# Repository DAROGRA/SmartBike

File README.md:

# SmartBike
 Proyecto Sistemas Embebidos, para mayor informacion visita la Wiki del proyecto

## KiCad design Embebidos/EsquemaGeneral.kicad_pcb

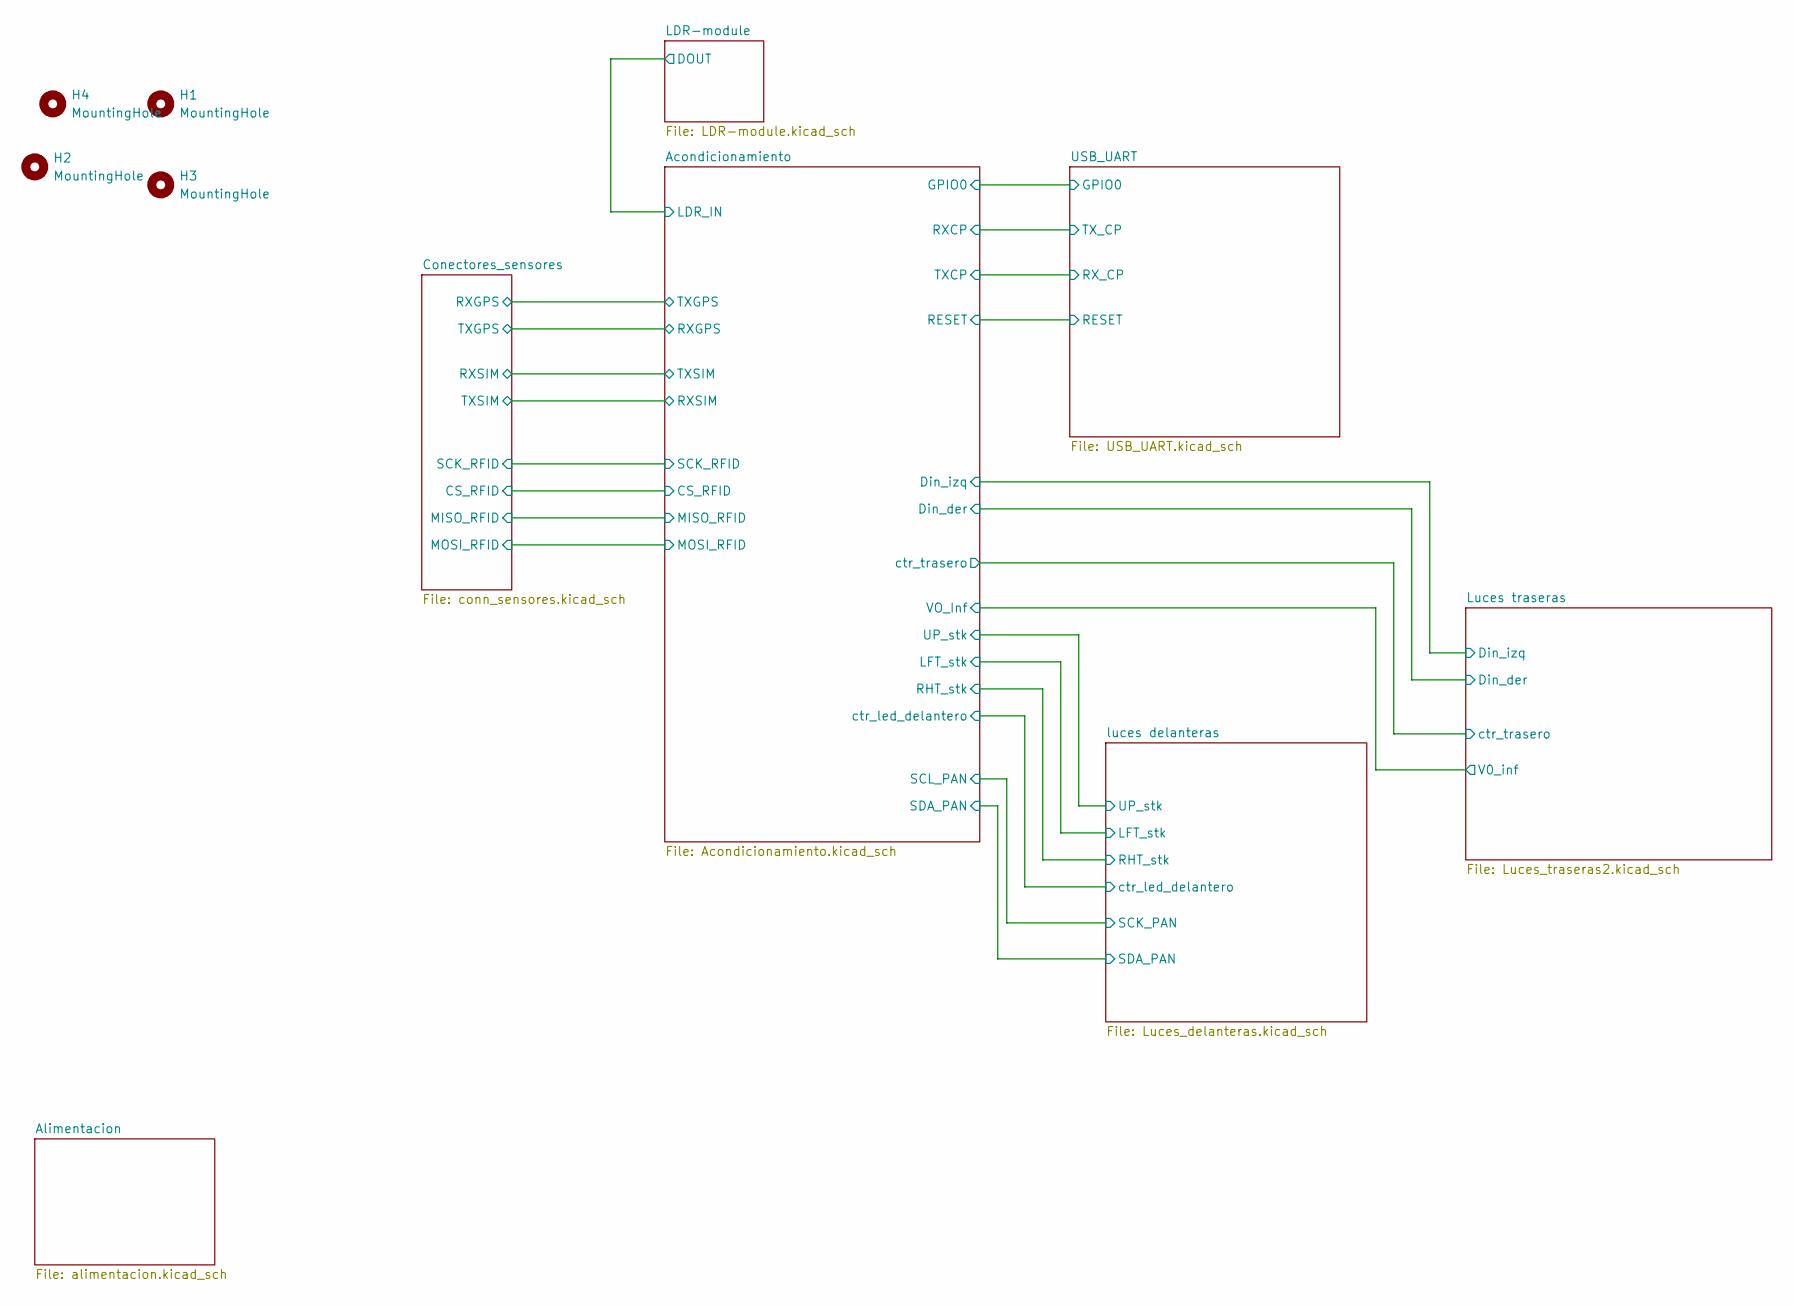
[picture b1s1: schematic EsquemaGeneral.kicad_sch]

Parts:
H1, H2, H3, H4: MountingHole; MountingHole_2.2mm_M2

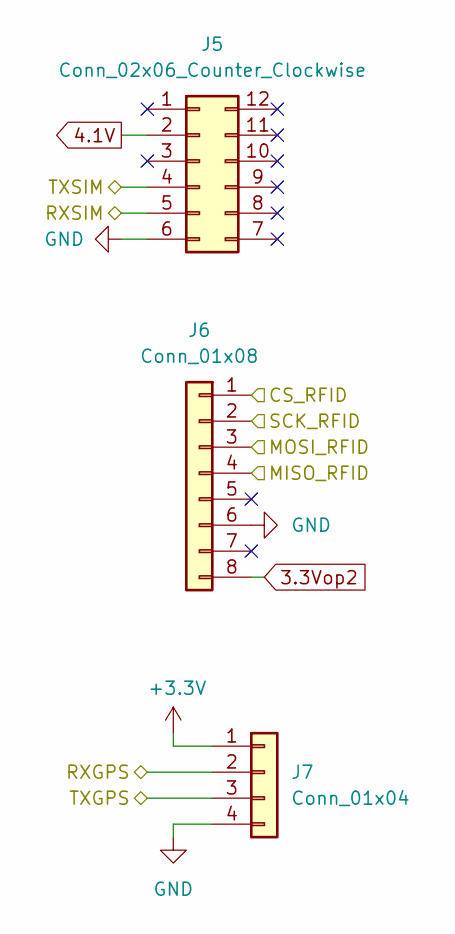
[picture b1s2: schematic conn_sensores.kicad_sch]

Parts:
J5: Conn_02x06_Counter_Clockwise; sim800l
J6: Conn_01x08; JST_EH_S8B-EH_1x08_P2.50mm_Horizontal
J7: Conn_01x04; JST_EH_B4B-EH-A_1x04_P2.50mm_Vertical

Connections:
3.3Vop2: J6.8; also elsewhere on the board
4.1V: J5.2; also elsewhere on the board
+3.3V: J7.1; also elsewhere on the board
/Acondicionamiento/CS_RFID: J6.1; also elsewhere on the board
/Acondicionamiento/MISO_RFID: J6.4; also elsewhere on the board
/Acondicionamiento/MOSI_RFID: J6.3; also elsewhere on the board
/Acondicionamiento/RXGPS: J7.3; also elsewhere on the board
/Acondicionamiento/RXSIM: J5.4; also elsewhere on the board
/Acondicionamiento/SCK_RFID: J6.2; also elsewhere on the board
/Acondicionamiento/TXGPS: J7.2; also elsewhere on the board
/Acondicionamiento/TXSIM: J5.5; also elsewhere on the board
GND: J5.6, J6.6, J7.4; also elsewhere on the board

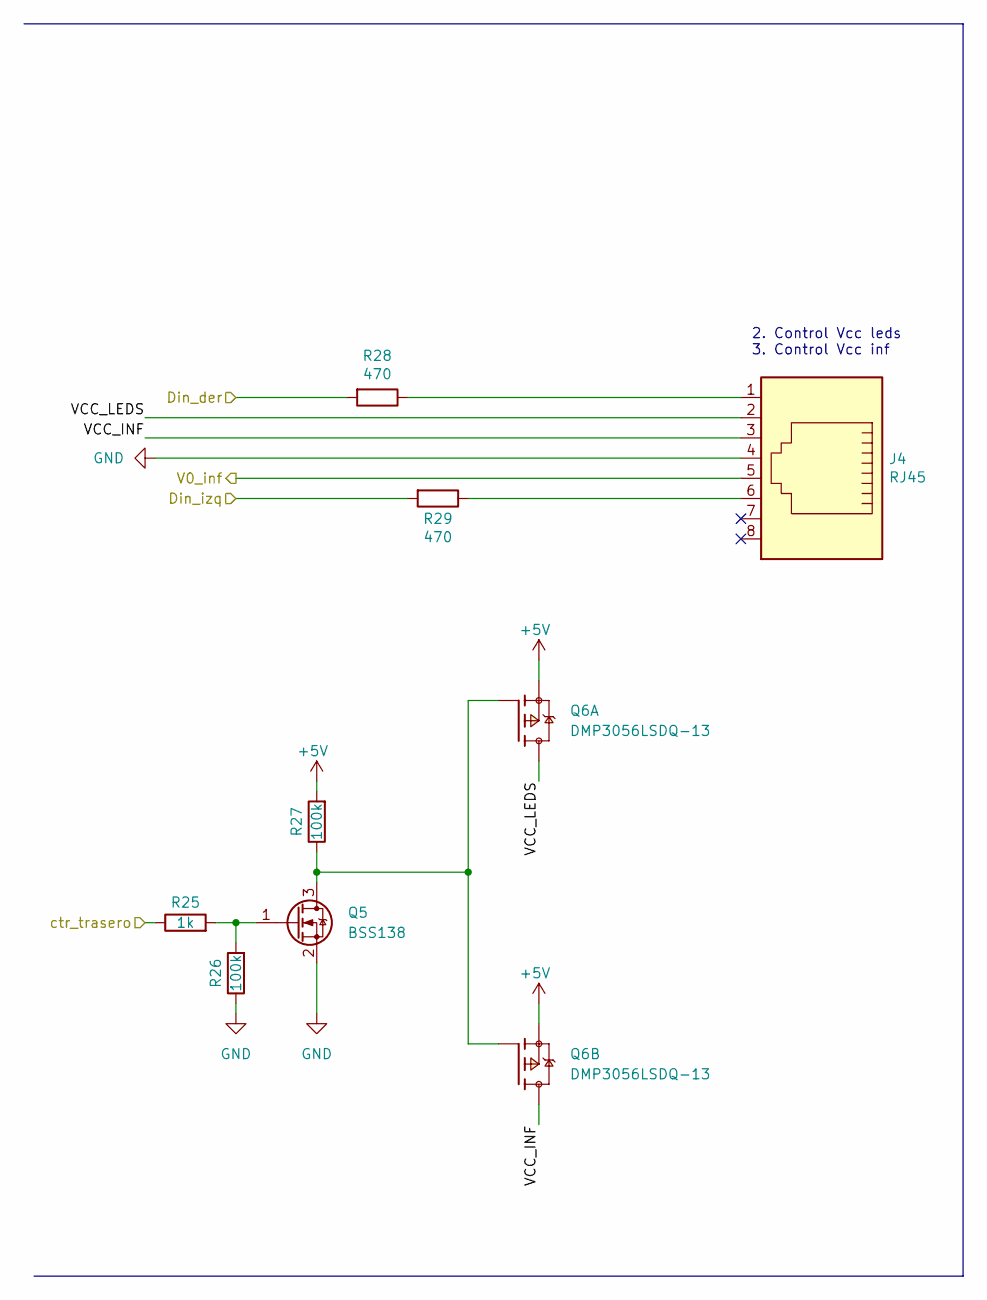
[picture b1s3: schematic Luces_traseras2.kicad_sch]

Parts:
J4: RJ45; RJ45_Amphenol_54602-x08_Horizontal
Q5: BSS138; SOT-23
Q6: DMP3056LSDQ-13; SOIC127P600X175-8N; PARTREV 1-2
R25: 1k; R_0805_2012Metric_Pad1.20x1.40mm_HandSolder
R26, R27: 100k; R_0805_2012Metric_Pad1.20x1.40mm_HandSolder
R28, R29: 470; R_0805_2012Metric_Pad1.20x1.40mm_HandSolder

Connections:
+5V: Q6.1, Q6.3, R27.2; also elsewhere on the board
/Acondicionamiento/Din_der: R28.2; also elsewhere on the board
/Acondicionamiento/Din_izq: R29.2; also elsewhere on the board
/Acondicionamiento/VO_Inf: J4.5; also elsewhere on the board
/Acondicionamiento/ctr_trasero: R25.1; also elsewhere on the board
/Luces traseras/VCC_INF: J4.3, Q6.5, Q6.6
/Luces traseras/VCC_LEDS: J4.2, Q6.7, Q6.8
GND: J4.4, Q5.2 (S), R26.1; also elsewhere on the board
unnamed: J4.1, R28.1
unnamed: J4.6, R29.1
unnamed: Q5.1 (G), R25.2, R26.2
unnamed: Q5.3 (D), Q6.2, Q6.4, R27.1

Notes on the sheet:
2. Control Vcc leds 3. Control Vcc inf

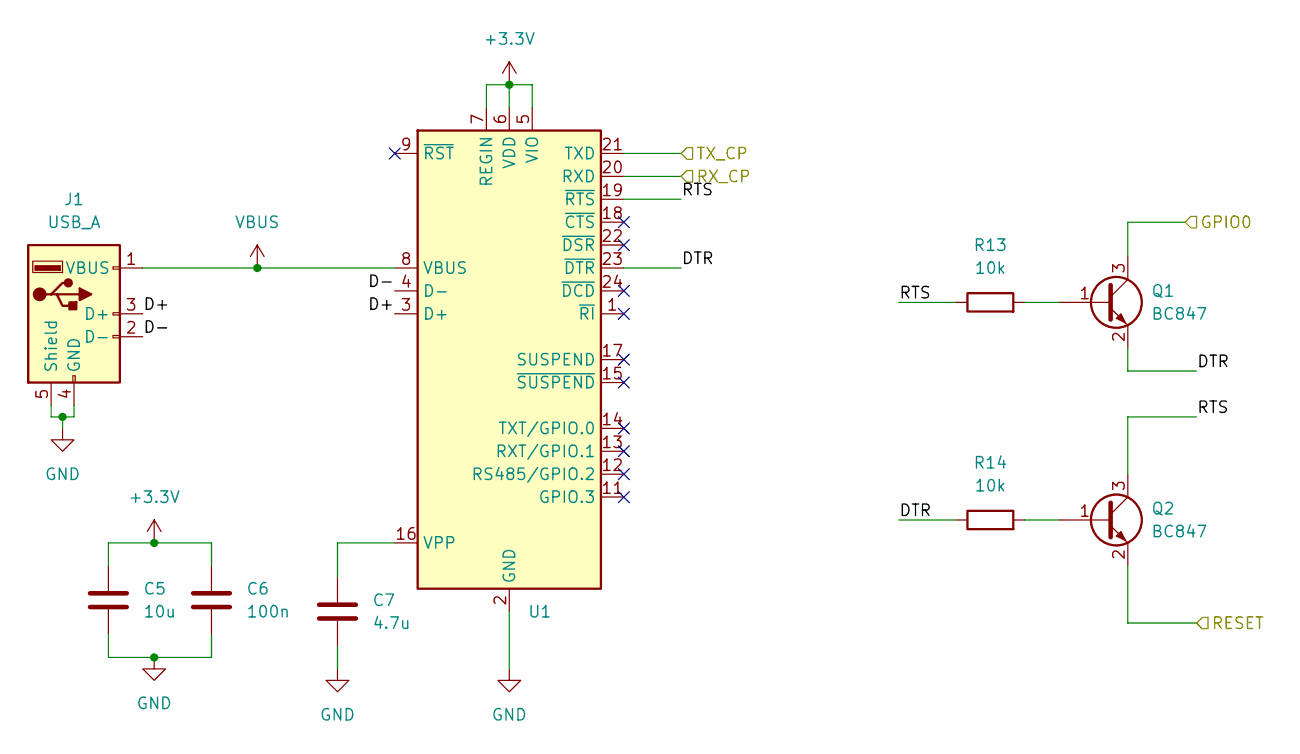
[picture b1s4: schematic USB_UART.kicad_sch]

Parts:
C5: 10u; C_0805_2012Metric_Pad1.18x1.45mm_HandSolder
C6: 100n; C_0805_2012Metric_Pad1.18x1.45mm_HandSolder
C7: 4.7u; C_0805_2012Metric_Pad1.18x1.45mm_HandSolder
J1: USB_A; USB_A_CNCTech_1001-011-01101_Horizontal
Q1, Q2: BC847; SOT23
R13, R14: 10k; R_0805_2012Metric_Pad1.20x1.40mm_HandSolder
U1: QFN50P400X400X80-25N

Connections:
+3.3V: C5.1, C6.1, U1.5 (VIO), U1.6 (VDD), U1.7 (REGIN); also elsewhere on the board
/Acondicionamiento/GPIO0: Q1.3 (C); also elsewhere on the board
/Acondicionamiento/RESET: Q2.2 (E); also elsewhere on the board
/Acondicionamiento/RXCP: U1.21 (TXD); also elsewhere on the board
/Acondicionamiento/TXCP: U1.20 (RXD); also elsewhere on the board
/USB_UART/D+: J1.3 (D+), U1.3 (D+)
/USB_UART/D-: J1.2 (D-), U1.4 (D-)
/USB_UART/DTR: Q1.2 (E), R14.1, U1.23 (~DTR)
/USB_UART/RTS: Q2.3 (C), R13.1, U1.19 (~RTS)
GND: C5.2, C6.2, C7.2, J1.4 (GND), J1.5 (Shield), U1.2 (GND), U1.25 (GND); also elsewhere on the board
unnamed: C7.1, U1.16 (VPP)
unnamed: Q1.1 (B), R13.2
unnamed: Q2.1 (B), R14.2
VBUS: J1.1 (VBUS), U1.8 (VBUS)

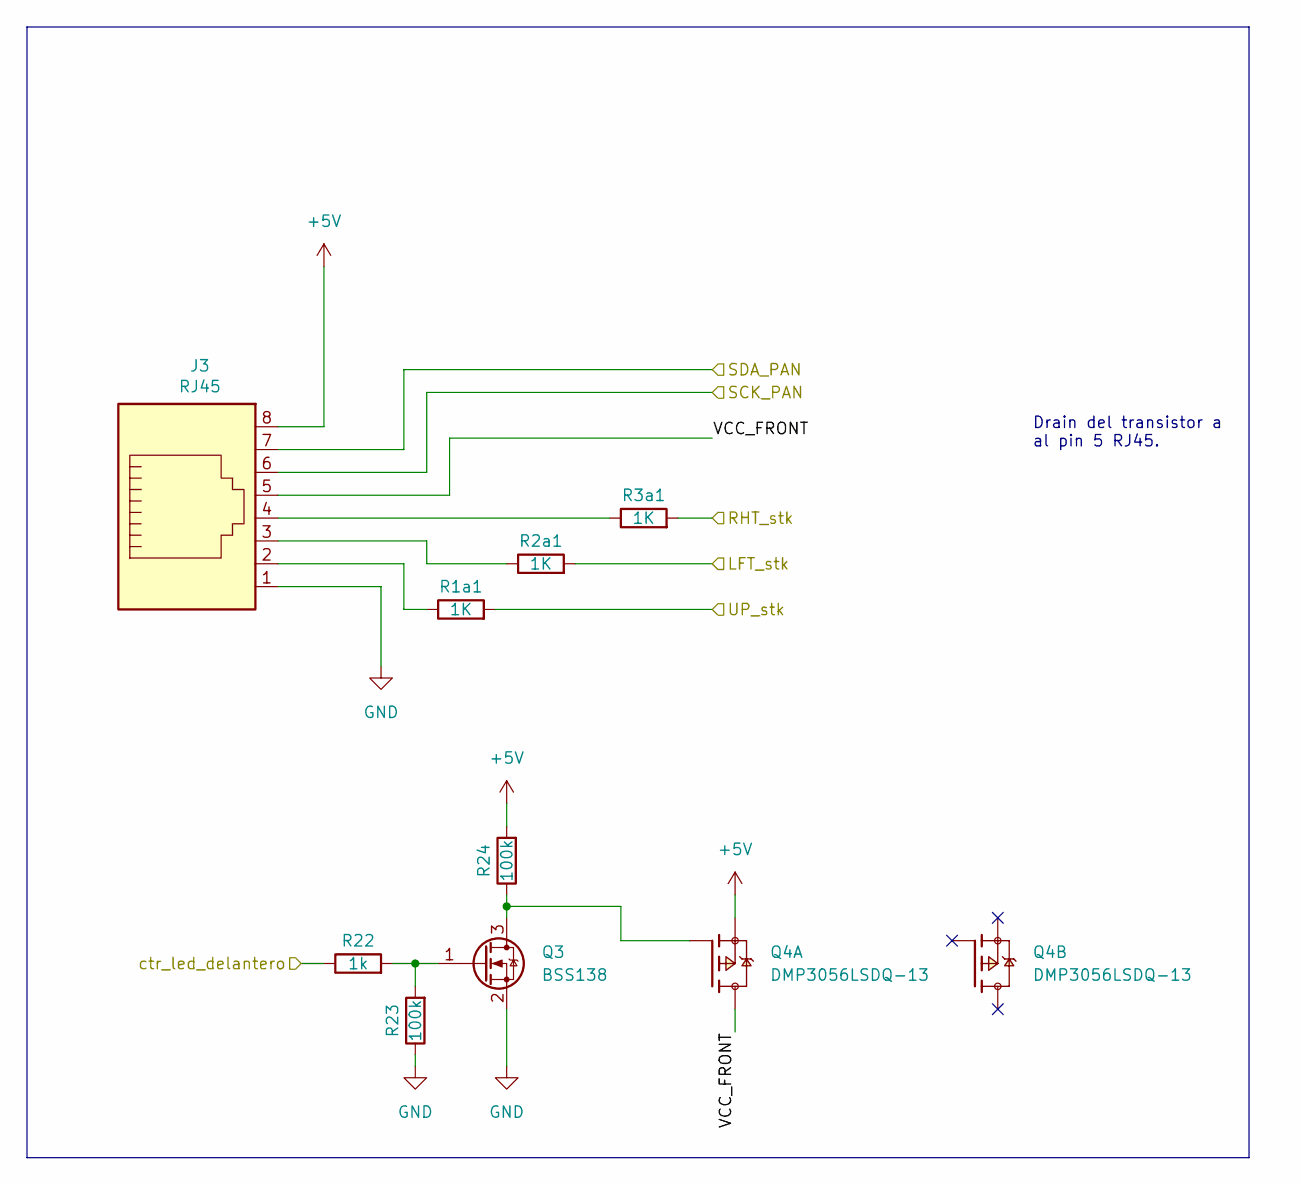
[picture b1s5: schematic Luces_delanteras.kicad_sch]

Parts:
J3: RJ45; RJ45_Amphenol_54602-x08_Horizontal
Q3: BSS138; SOT-23
Q4: DMP3056LSDQ-13; SOIC127P600X175-8N; PARTREV 1-2
R1a1, R2a1, R3a1: 1K; R_0805_2012Metric_Pad1.20x1.40mm_HandSolder
R22: 1k; R_0805_2012Metric_Pad1.20x1.40mm_HandSolder
R23, R24: 100k; R_0805_2012Metric_Pad1.20x1.40mm_HandSolder

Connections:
+5V: J3.8, Q4.1, R24.2; also elsewhere on the board
/Acondicionamiento/LFT_stk: R2a1.2; also elsewhere on the board
/Acondicionamiento/RHT_stk: R3a1.2; also elsewhere on the board
/Acondicionamiento/SCL_PAN: J3.6; also elsewhere on the board
/Acondicionamiento/SDA_PAN: J3.7; also elsewhere on the board
/Acondicionamiento/UP_stk: R1a1.2; also elsewhere on the board
/Acondicionamiento/ctr_led_delantero: R22.1; also elsewhere on the board
/luces delanteras/VCC_FRONT: J3.5, Q4.7, Q4.8
GND: J3.1, Q3.2 (S), R23.1; also elsewhere on the board
unnamed: J3.2, R1a1.1
unnamed: J3.3, R2a1.1
unnamed: J3.4, R3a1.1
unnamed: Q3.1 (G), R22.2, R23.2
unnamed: Q3.3 (D), Q4.2, R24.1

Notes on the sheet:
Drain del transistor a al pin 5 RJ45.

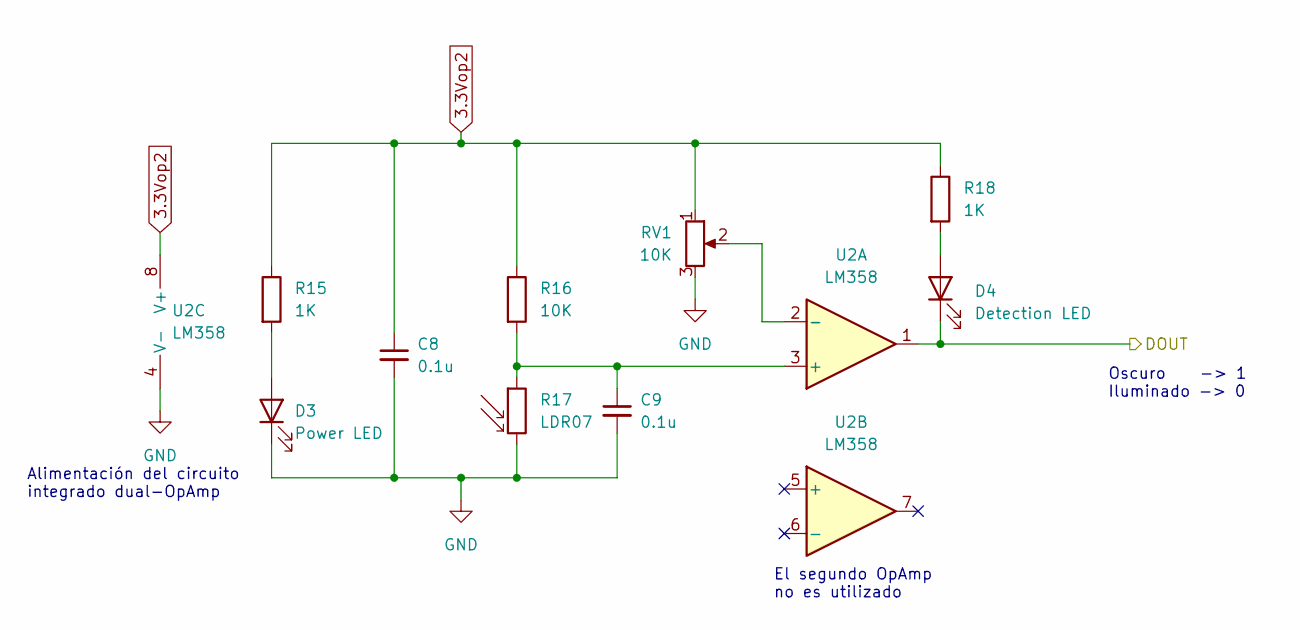
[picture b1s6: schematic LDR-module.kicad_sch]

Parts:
C8, C9: 0.1u; C_0805_2012Metric_Pad1.18x1.45mm_HandSolder
D3: Power LED; LED_0805_2012Metric_Pad1.15x1.40mm_HandSolder
D4: Detection LED; LED_0805_2012Metric_Pad1.15x1.40mm_HandSolder
R15, R18: 1K; R_0805_2012Metric_Pad1.20x1.40mm_HandSolder
R16: 10K; R_0805_2012Metric_Pad1.20x1.40mm_HandSolder
R17: LDR07; R_LDR_5.1x4.3mm_P3.4mm_Vertical
RV1: 10K; Potentiometer_Bourns_3386P_Vertical
U2: LM358; SOIC127P599X175-8N

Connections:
3.3Vop2: C8.1, R15.1, R16.1, R18.1, RV1.1, U2.8 (V+); also elsewhere on the board
/Acondicionamiento/LDR_IN: D4.1 (K), U2.1; also elsewhere on the board
GND: C8.2, C9.2, D3.1 (K), R17.2, RV1.3, U2.4 (V-); also elsewhere on the board
unnamed: C9.1, R16.2, R17.1, U2.3 (+)
unnamed: D3.2 (A), R15.2
unnamed: D4.2 (A), R18.2
unnamed: RV1.2, U2.2 (-)

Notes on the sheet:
El segundo OpAmp no es utilizado
Alimentación del circuito integrado dual-OpAmp
Oscuro -> 1 Iluminado -> 0

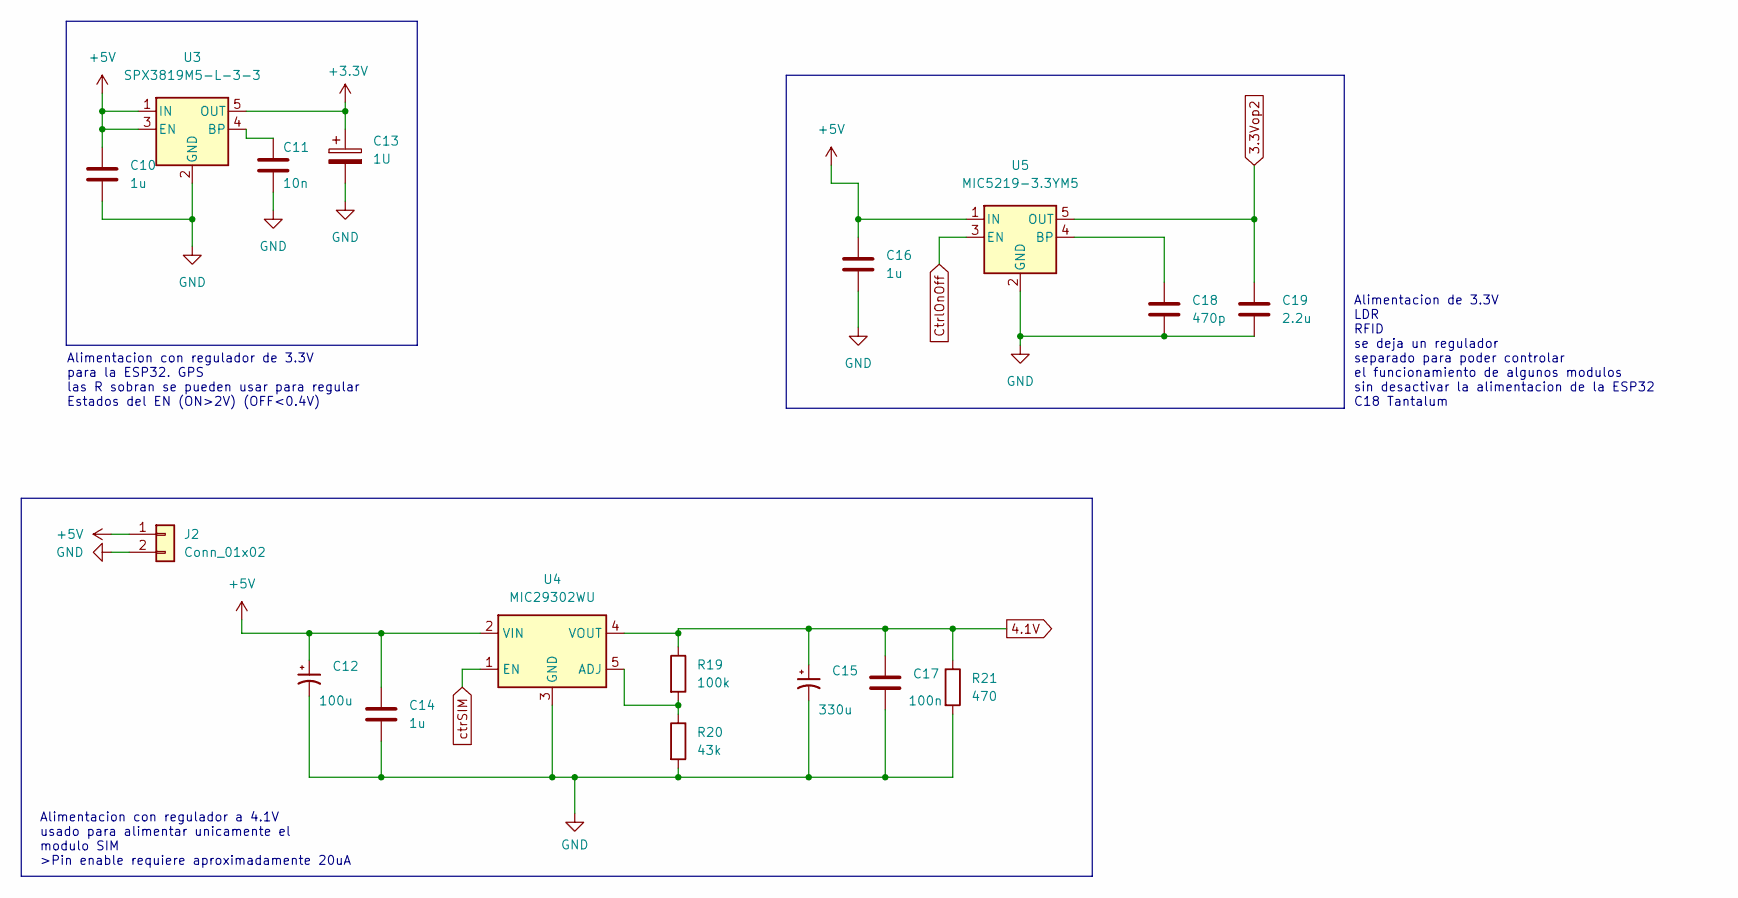
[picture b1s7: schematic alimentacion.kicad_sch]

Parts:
C10, C14, C16: 1u; C_0805_2012Metric_Pad1.18x1.45mm_HandSolder
C11: 10n; C_0805_2012Metric_Pad1.18x1.45mm_HandSolder
C12: 100u; CP_EIA-6032-28_Kemet-C_Pad2.25x2.35mm_HandSolder
C13: 1U; CP_EIA-3216-18_Kemet-A_Pad1.58x1.35mm_HandSolder
C15: 330u; CP_Elec_8x10.5
C17: 100n; C_0805_2012Metric_Pad1.18x1.45mm_HandSolder
C18: 470p; C_0805_2012Metric_Pad1.18x1.45mm_HandSolder
C19: 2.2u; CP_EIA-3216-18_Kemet-A_Pad1.58x1.35mm_HandSolder
J2: Conn_01x02; JST_EH_S2B-EH_1x02_P2.50mm_Horizontal
R19: 100k; R_0805_2012Metric_Pad1.20x1.40mm_HandSolder
R20: 43k; R_1206_3216Metric_Pad1.30x1.75mm_HandSolder
R21: 470; R_0805_2012Metric_Pad1.20x1.40mm_HandSolder
U3: SPX3819M5-L-3-3; SOT-23-5
U4: MIC29302WU; TO-263-5_TabPin3
U5: MIC5219-3.3YM5; SOT-23-5

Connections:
3.3Vop2: C19.1, U5.5 (OUT); also elsewhere on the board
4.1V: C15.1, C17.1, R19.1, R21.1, U4.4 (VOUT); also elsewhere on the board
+3.3V: C13.1, U3.5 (OUT); also elsewhere on the board
+5V: C10.1, C12.1, C14.1, C16.1, J2.1, U3.1 (IN), U3.3 (EN), U4.2 (VIN), U5.1 (IN); also elsewhere on the board
CtrlOnOff: U5.3 (EN); also elsewhere on the board
GND: C10.2, C11.2, C12.2, C13.2, C14.2, C15.2, C16.2, C17.2, C18.2, C19.2, J2.2, R20.2, R21.2, U3.2 (GND), U4.3 (GND), U5.2 (GND); also elsewhere on the board
unnamed: C11.1, U3.4 (BP)
unnamed: C18.1, U5.4 (BP)
unnamed: R19.2, R20.1, U4.5 (ADJ)
ctrSIM: U4.1 (EN); also elsewhere on the board

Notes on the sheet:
Alimentacion de 3.3V LDR RFID se deja un regulador separado para poder controlar el funcionamiento de algunos modulos sin desactivar la alimentacion de la ESP32 C18 Tantalum
Alimentacion con regulador a 4.1V usado para alimentar unicamente el modulo SIM >Pin enable requiere aproximadamente 20uA
Alimentacion con regulador de 3.3V para la ESP32. GPS las R sobran se pueden usar para regular Estados del EN (ON>2V) (OFF<0.4V)

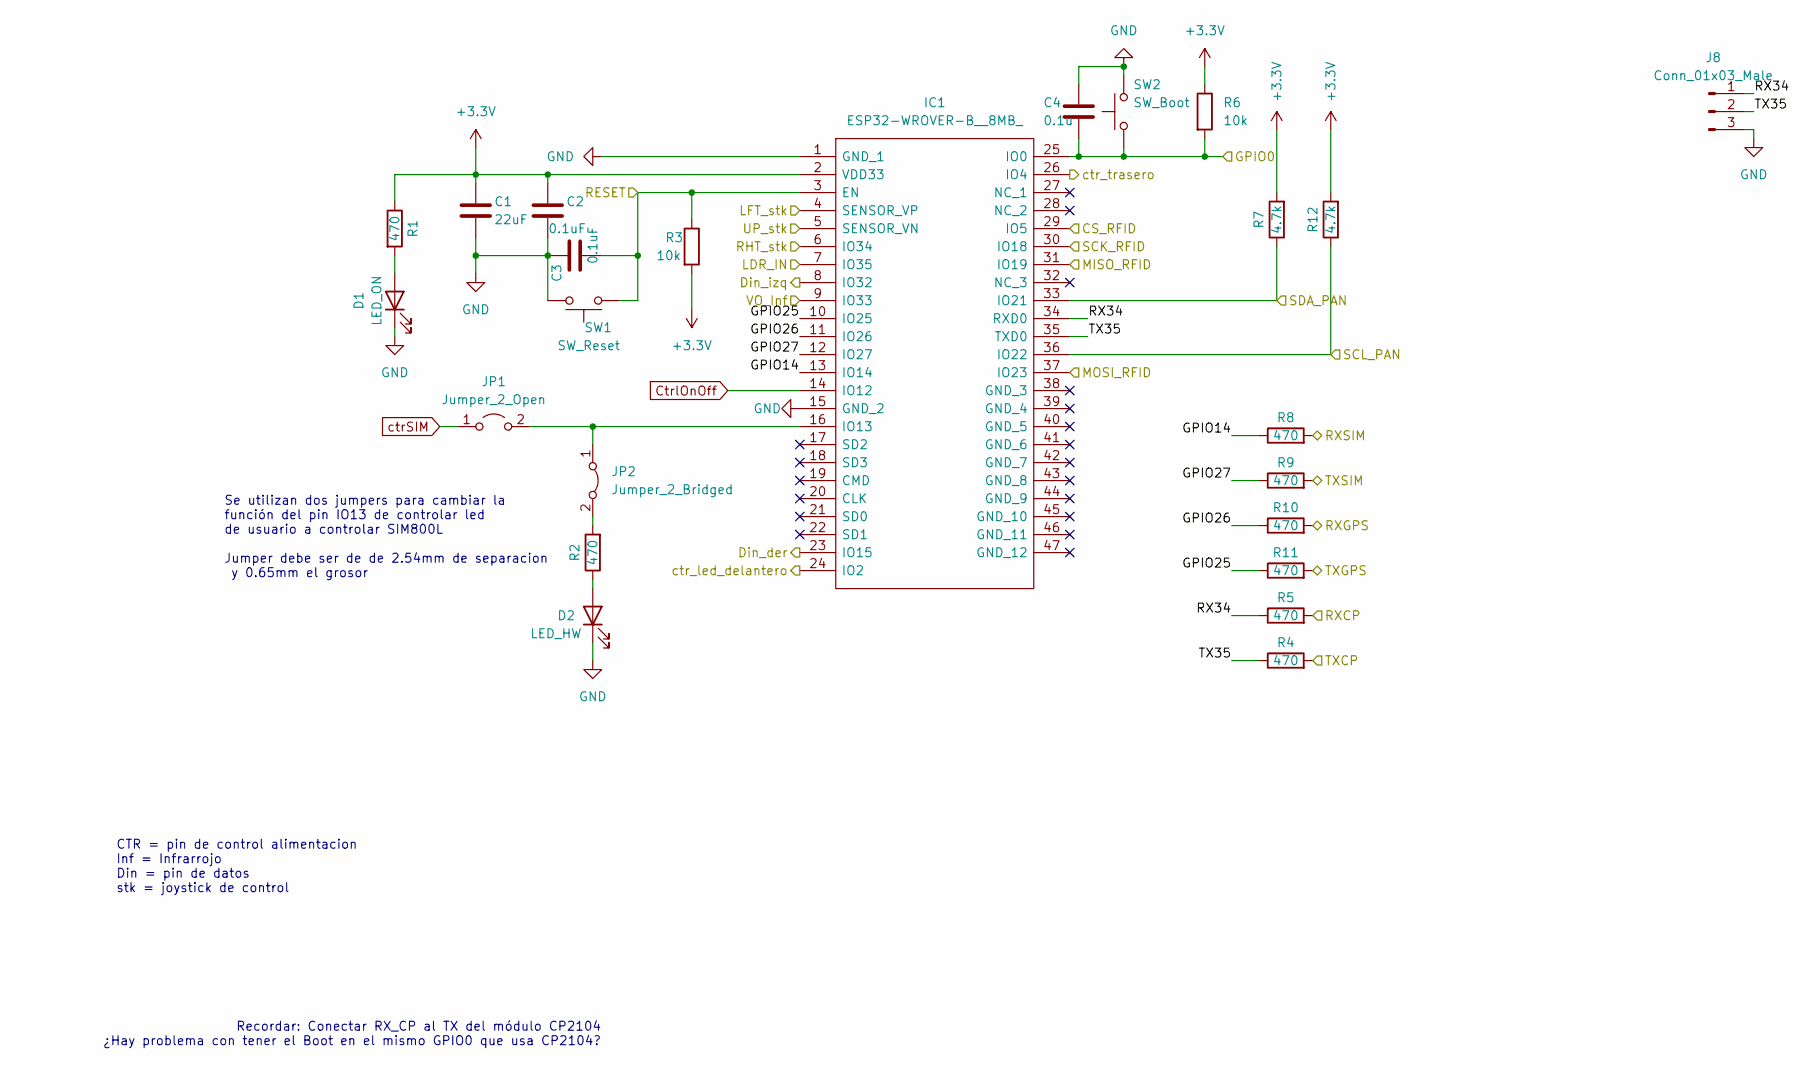
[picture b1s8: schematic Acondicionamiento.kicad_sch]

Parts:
C1: 22uF; C_0805_2012Metric_Pad1.18x1.45mm_HandSolder
C2, C3: 0.1uF; C_0805_2012Metric_Pad1.18x1.45mm_HandSolder
C4: 0.1u; C_0805_2012Metric_Pad1.18x1.45mm_HandSolder
D1: LED_ON; LED_0805_2012Metric_Pad1.15x1.40mm_HandSolder
D2: LED_HW; LED_0805_2012Metric_Pad1.15x1.40mm_HandSolder
IC1: ESP32-WROVER-B__8MB_; ESP32WROVERB8MB; Manufacturer_Part_Number ESP32-WROVER-B (8MB); Mouser Part Number 356-ESP32-WRO-B(8MB)
J8: Conn_01x03_Male; PinHeader_1x03_P2.54mm_Vertical
JP1: Jumper_2_Open; PinHeader_1x02_P2.54mm_Vertical
JP2: Jumper_2_Bridged; PinHeader_1x02_P2.54mm_Vertical
R1, R2, R4, R5, R8, R9, R10, R11: 470; R_0805_2012Metric_Pad1.20x1.40mm_HandSolder
R3, R6: 10k; R_0805_2012Metric_Pad1.20x1.40mm_HandSolder
R7, R12: 4.7k; R_0805_2012Metric_Pad1.20x1.40mm_HandSolder
SW1: SW_Reset; pulsador
SW2: SW_Boot; pulsador

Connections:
+3.3V: C1.1, C2.1, IC1.2 (VDD33), R1.1, R3.2, R6.1, R7.2, R12.2; also elsewhere on the board
/Acondicionamiento/CS_RFID: IC1.29 (IO5); also elsewhere on the board
/Acondicionamiento/Din_der: IC1.23 (IO15); also elsewhere on the board
/Acondicionamiento/Din_izq: IC1.8 (IO32); also elsewhere on the board
/Acondicionamiento/GPIO0: C4.2, IC1.25 (IO0), R6.2, SW2.1; also elsewhere on the board
/Acondicionamiento/GPIO14: IC1.13 (IO14), R8.1
/Acondicionamiento/GPIO25: IC1.10 (IO25), R11.1
/Acondicionamiento/GPIO26: IC1.11 (IO26), R10.1
/Acondicionamiento/GPIO27: IC1.12 (IO27), R9.1
/Acondicionamiento/LDR_IN: IC1.7 (IO35); also elsewhere on the board
/Acondicionamiento/LFT_stk: IC1.4 (SENSOR_VP); also elsewhere on the board
/Acondicionamiento/MISO_RFID: IC1.31 (IO19); also elsewhere on the board
/Acondicionamiento/MOSI_RFID: IC1.37 (IO23); also elsewhere on the board
/Acondicionamiento/RESET: C3.2, IC1.3 (EN), R3.1, SW1.1; also elsewhere on the board
/Acondicionamiento/RHT_stk: IC1.6 (IO34); also elsewhere on the board
/Acondicionamiento/RX34: IC1.34 (RXD0), J8.1, R5.1
/Acondicionamiento/RXCP: R5.2; also elsewhere on the board
/Acondicionamiento/RXGPS: R10.2; also elsewhere on the board
/Acondicionamiento/RXSIM: R8.2; also elsewhere on the board
/Acondicionamiento/SCK_RFID: IC1.30 (IO18); also elsewhere on the board
/Acondicionamiento/SCL_PAN: IC1.36 (IO22), R12.1; also elsewhere on the board
/Acondicionamiento/SDA_PAN: IC1.33 (IO21), R7.1; also elsewhere on the board
/Acondicionamiento/TX35: IC1.35 (TXD0), J8.2, R4.1
/Acondicionamiento/TXCP: R4.2; also elsewhere on the board
/Acondicionamiento/TXGPS: R11.2; also elsewhere on the board
/Acondicionamiento/TXSIM: R9.2; also elsewhere on the board
/Acondicionamiento/UP_stk: IC1.5 (SENSOR_VN); also elsewhere on the board
/Acondicionamiento/VO_Inf: IC1.9 (IO33); also elsewhere on the board
/Acondicionamiento/ctr_led_delantero: IC1.24 (IO2); also elsewhere on the board
/Acondicionamiento/ctr_trasero: IC1.26 (IO4); also elsewhere on the board
CtrlOnOff: IC1.14 (IO12); also elsewhere on the board
GND: C1.2, C2.2, C3.1, C4.1, D1.1 (K), D2.1 (K), IC1.1 (GND_1), IC1.15 (GND_2), J8.3, SW1.2, SW2.2; also elsewhere on the board
unnamed: D1.2 (A), R1.2
unnamed: D2.2 (A), R2.1
unnamed: IC1.16 (IO13), JP1.2 (B), JP2.1 (A)
unnamed: JP2.2 (B), R2.2
ctrSIM: JP1.1 (A); also elsewhere on the board

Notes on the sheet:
Recordar: Conectar RX_CP al TX del módulo CP2104 ¿Hay problema con tener el Boot en el mismo GPIO0 que usa CP2104?
Se utilizan dos jumpers para cambiar la función del pin IO13 de controlar led de usuario a controlar SIM800L Jumper debe ser de de 2.54mm de separacion y 0.65mm el grosor
CTR = pin de control alimentacion Inf = Infrarrojo Din = pin de datos stk = joystick de control

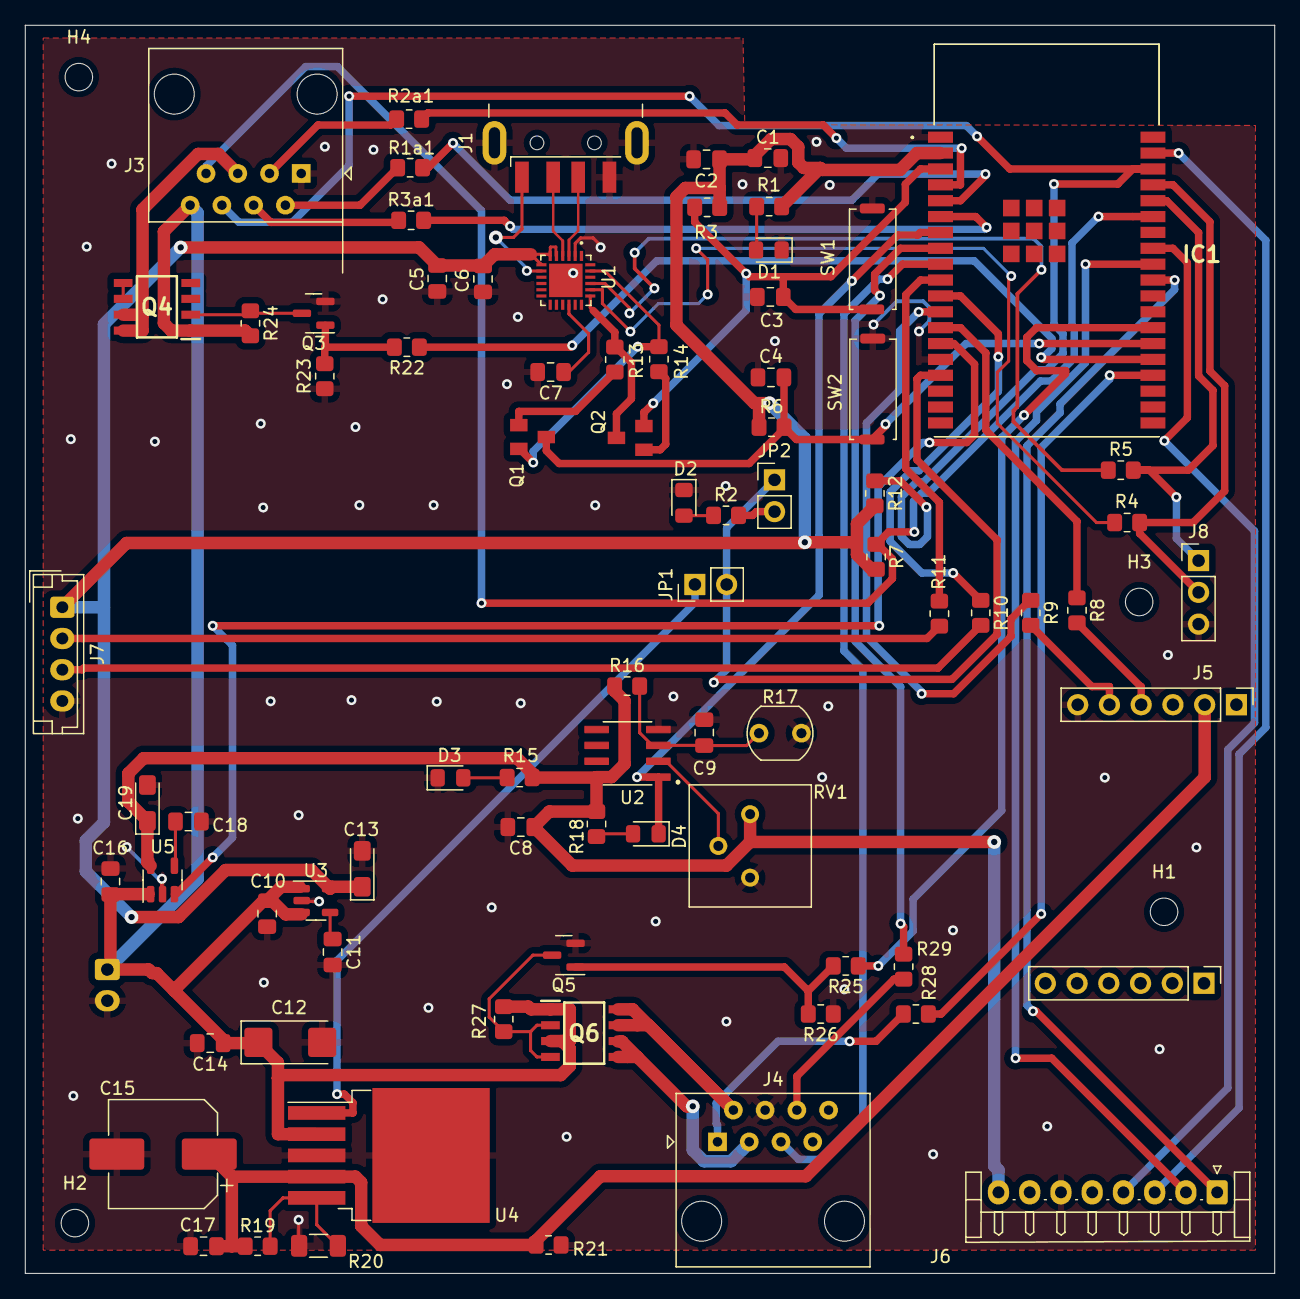
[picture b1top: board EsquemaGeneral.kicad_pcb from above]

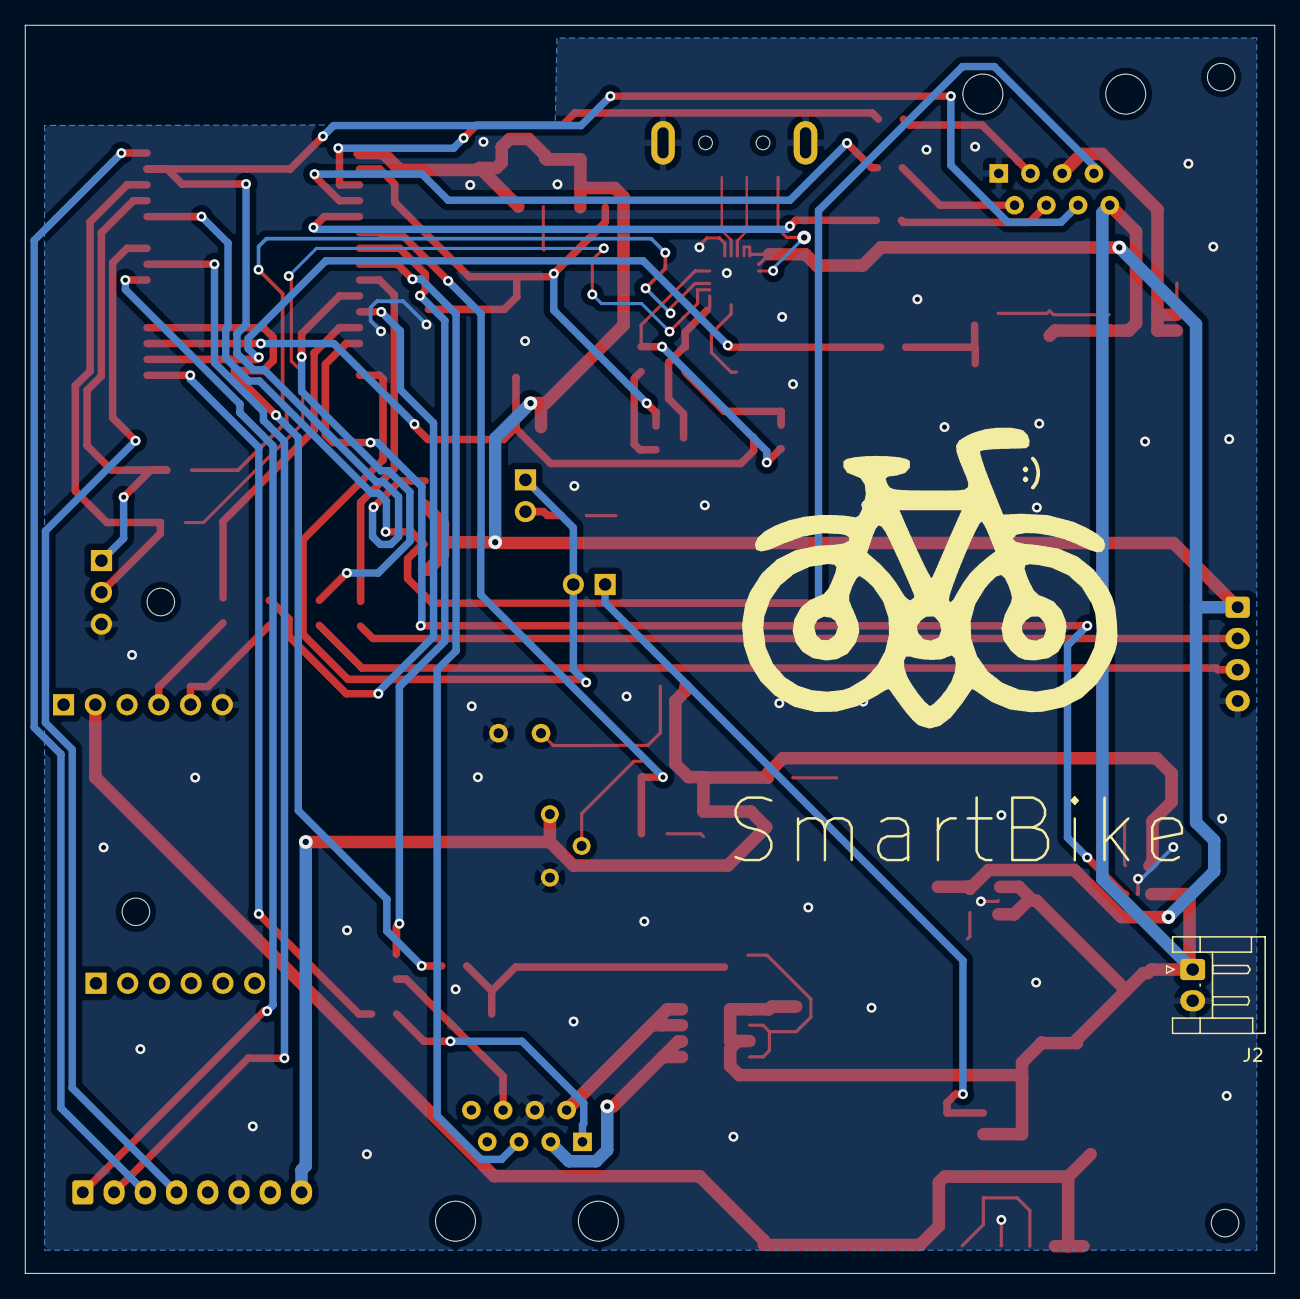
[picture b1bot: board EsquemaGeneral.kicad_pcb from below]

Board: 2 copper layers, 100.0 x 99.9 mm, 85 parts (2 on the bottom side), 67 nets.

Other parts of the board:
:): LOGO; Logonuevo

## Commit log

2022-09-01 Add files via upload
    Algunos Datasheets
2022-09-08 Add files via upload
    sensor infrarrojo
2022-09-29 Prueba
2022-10-02 hola
2022-10-04 incluí ESP32 y USB_UART
2022-10-04 Create p
2022-10-04 modificado
2022-10-04 LDR module adittion
2022-10-04 Alimentacion
2022-10-04 ultimaalimentacionporhoy
2022-10-05 Corrección de anotaciones
2022-10-06 Luces delanteras, traseras, pantalla, e infrarrojo
2022-10-11 actualizacion
2022-10-11 errores_electricos
2022-10-11 error_elc
2022-10-11 anotaciones_fix
2022-10-11 marcas_x
2022-10-11 LDR_69Errores
2022-10-11 Transistores
2022-10-11 Dtaasheet mosfetP
2022-10-11 nada
2022-10-11 huellas
2022-10-11 pruebas
2022-10-11 conectoresRFySIM
2022-10-11 Mosfet Luces
2022-10-11 COnecxion
2022-10-12 mejoras alimentacion
2022-10-13 se agrego el Bonito
2022-10-13 agregados los jumpers
2022-10-13 correccion lul
2022-10-13 cambio LDR
2022-10-13 arreglo FP
2022-10-13 MAS fp
2022-10-13 transistores traseros
2022-10-13 Cambio de anotacion y Vcc ldr
2022-10-13 Cambios varios
    -Conectores movidos a nueva hoja jerarquica
    -Transistores DMP colocados en lices delanteras
    -Jumpers ubicados para el uso del pin IO13 para SIM800 y LEDHW
    -Etiqueta de "no conectado" ubicada en USB_UART
2022-10-13 autosaves eliminados
2022-10-17 ajustes
2022-10-17 noseuwu
2022-10-17 nosex2
2022-10-17 fpesp
2022-10-17 huellass
2022-10-17 cache???
2022-10-17 Correccion Errores
2022-10-17 huellasss
2022-10-17 arreglos
2022-10-17 Correccion errores y huellas leds LDR
2022-10-18 cache
2022-10-18 arreglo
2022-10-18 Anotaciones
2022-10-18 errorpeque
2022-10-18 alimentacionx200000
2022-10-18 Recuperacion
2022-10-18 Errores huellas
2022-10-18 anarquia
2022-10-18 Operacion Fenix
2022-10-18 Backup uwu
2022-10-18 panic
    no otra vez uwu
2022-10-18 porquesi
2022-10-18 organizando
2022-10-18 backups
2022-10-18 mas orden
2022-10-19 orden pcb
2022-10-19 se agregan cositasss
2022-10-19 mas orden en la ubicacion de huellas
2022-10-20 ruteado pero toca corregirlo
2022-10-21 mejora ubicacion de huellas
2022-10-21 pistas gordas :(
2022-10-21 no se uwu
2022-10-21 Cambio huella Capacitor
2022-10-21 eliminar pistas para volver a intetar
    :c
2022-10-21 siiiiiiiiii
2022-10-21 Tierras
2022-10-22 arreglo del uart feo y pequeño
    Gracias profeee por si acaso lee estooooo
2022-10-22 arreglo serigrafias y rutas
2022-10-22 ultimas modificaciones
2022-10-22 queda un error
2022-10-22 fix: track clearance cp2102x fixed
2022-10-22 Revert "ai"
    This reverts commit 0a330e204fbdc8aac4303f8de6fa14c1261b352c, reversing
    changes made to c8426c30f6ece7c381f77537cb0de3e4f23fbe4e.
2022-10-22 Operacion salvar
2022-10-22 a 1 error de terminar
2022-10-22 EN BUSQUEDA DEL ERROR PERDIDO
2022-10-22 Maldigo a la caché
2022-10-22 siuuuuuuuuuuuuuuuuuuuuuuuuuuuuuuuuuu :')
2022-10-22 Aaaaaaaaaaaaaaa la cache es demasiado fuerte
2022-10-22 por si las moscas
2022-10-22 Pines programacon de emergencia
2022-10-22 Lista para los chinos
2022-10-22 para los chinos con logo
2022-10-22 Gerbers generados
    Cada vez más cerca
2022-10-22 X somos chavos
2022-10-22 Aaaaaaaaaaaaaaaaa
2022-10-24 LOGO AGREGADO
2023-10-30 No me funen
    Perdoname cristo
2023-11-05 Rev alimentacion
2023-11-07 autosave
